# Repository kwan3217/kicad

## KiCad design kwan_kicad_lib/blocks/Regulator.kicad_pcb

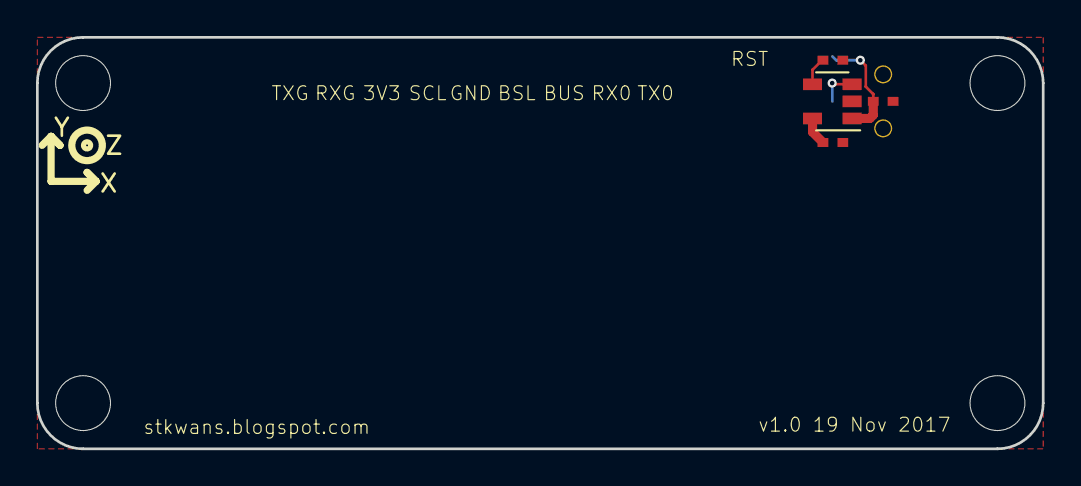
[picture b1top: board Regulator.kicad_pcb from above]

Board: 2 copper layers, 55.9 x 22.9 mm, 10 parts (0 on the bottom side), 5 nets.

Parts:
C704: 1uF; SMD_0402
C714: 100nF; SMD_0402
C715: 4.7nF; SMD_0402
JP1, JP2, JP4, JP5: STAND-OFFTIGHT; STAND-OFF-TIGHT
S701: SPDT; SWITCH_DPDT_AZY0202
U501: MPU9250; Axis
U701: 3.3V; SOT-23-5

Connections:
/BYP: C714.1, U701.4
/GND: C704.2, C714.2, C715.2, S701.3, U701.2
/PWR_EN: S701.2, U701.3
/VCC: C715.1, U701.5
/VRAW: C704.1, S701.1, U701.1

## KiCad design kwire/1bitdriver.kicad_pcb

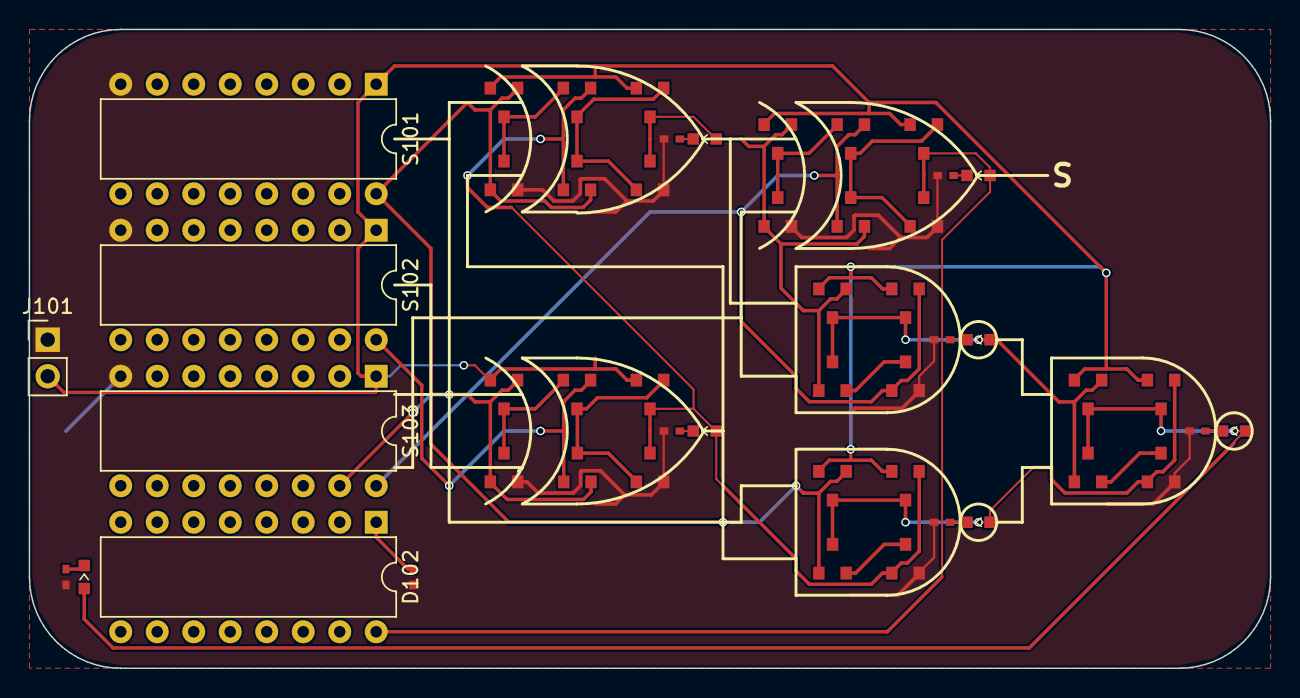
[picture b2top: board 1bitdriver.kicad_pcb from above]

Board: 2 copper layers, 86.4 x 44.5 mm, 50 parts (0 on the bottom side), 29 nets.

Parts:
D101: K; D_0603
D102: S; DIP-16_W7.62mm
D401, D501, D601, D701, D801, D901: LED_Small; D_0603
J101: CONN_01X02; Pin_Header_Straight_1x02_Pitch2.54mm
Q401, Q404, Q501, Q504, Q601, Q604, Q701, Q703, Q705, Q801, Q803, Q805, Q901, Q903, Q905: PMOS; SOT-23
Q402, Q403, Q502, Q503, Q602, Q603, Q702, Q704, Q706, Q802, Q804, Q806, Q902, Q904, Q906: NMOS; SOT-23
R101, R102, R401, R501, R601, R701, R801, R901: RESISTOR; SMD_0402
S101: A; DIP-16_W7.62mm
S102: B; DIP-16_W7.62mm
S103: C; DIP-16_W7.62mm

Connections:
/A: Q501.1, Q502.1, Q701.1, Q702.1, Q704.2, S101.16
/B: Q903.1, Q904.1, S102.16
/C: Q403.1, Q404.1, Q803.1, Q804.1, S103.16
/K: D101.2, D601.2, Q601.3, Q602.3, Q604.3
/S: D102.16, D801.2, Q805.3, Q806.3
/SUB: Q901.1, Q902.1, Q904.2, S103.15
/bit0/adder/#AandB: D501.2, Q501.3, Q502.3, Q504.3, Q603.1, Q604.1
/bit0/adder/#AxorBandC: D401.2, Q401.3, Q402.3, Q404.3, Q601.1, Q602.1
/bit0/adder/AxorB: D701.2, Q401.1, Q402.1, Q705.3, Q706.3, Q801.1, Q802.1, Q804.2
/bit0/adder/B: D901.2, Q503.1, Q504.1, Q703.1, Q704.1, Q905.3, Q906.3
GND: J101.1, Q403.2, Q503.2, Q603.2, Q702.2, Q706.2, Q802.2, Q806.2, Q902.2, Q906.2, R101.2, R102.2, R401.2, R501.2, R601.2, R701.2, R801.2, R901.2, S101.8, S102.8, S103.8
unnamed: D101.1, R101.1
unnamed: D102.1, R102.1
unnamed: D401.1, R401.1
unnamed: D501.1, R501.1
unnamed: D601.1, R601.1
unnamed: D701.1, R701.1
unnamed: D801.1, R801.1
unnamed: D901.1, R901.1
unnamed: Q402.2, Q403.3
unnamed: Q502.2, Q503.3
unnamed: Q602.2, Q603.3
unnamed: Q701.3, Q702.3, Q703.2
unnamed: Q703.3, Q704.3, Q705.1, Q706.1
unnamed: Q801.3, Q802.3, Q803.2
unnamed: Q803.3, Q804.3, Q805.1, Q806.1
unnamed: Q901.3, Q902.3, Q903.2
unnamed: Q903.3, Q904.3, Q905.1, Q906.1
VCC: J101.2, Q401.2, Q404.2, Q501.2, Q504.2, Q601.2, Q604.2, Q701.2, Q705.2, Q801.2, Q805.2, Q901.2, Q905.2, S101.1, S102.1, S103.1

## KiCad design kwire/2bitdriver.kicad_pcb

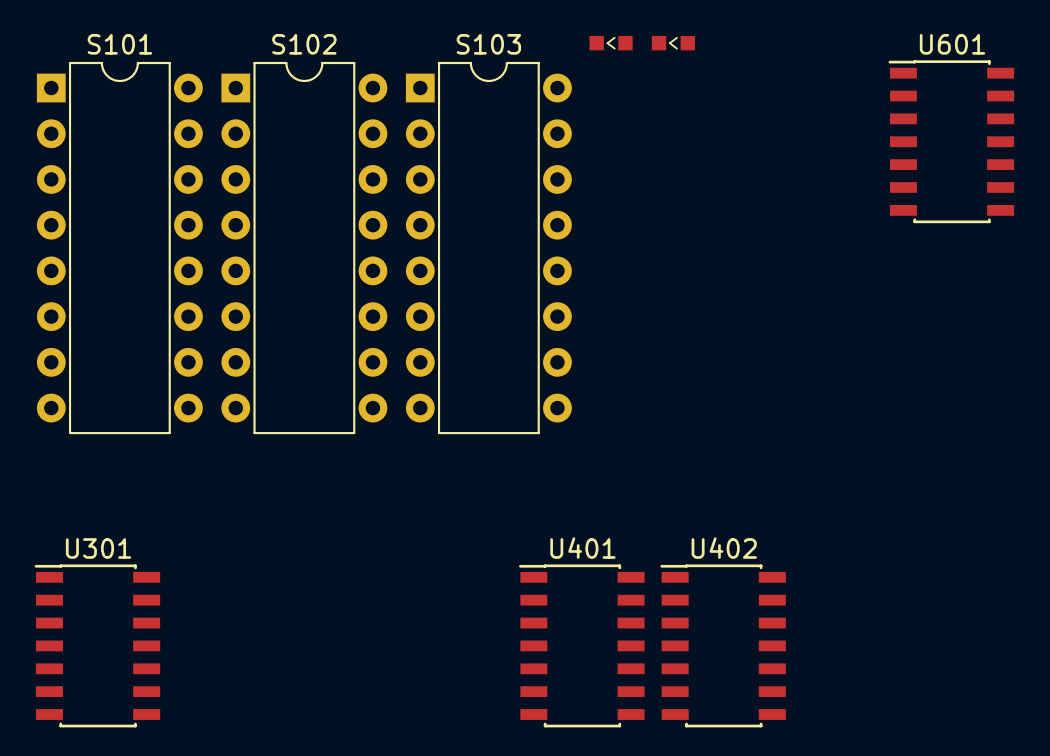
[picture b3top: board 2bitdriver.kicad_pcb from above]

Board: 2 copper layers, 9 parts (0 on the bottom side), 19 nets, no tracks yet.

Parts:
D101: K; D_0603
D102: S; D_0603
S101: A; DIP-16_W7.62mm
S102: B; DIP-16_W7.62mm
S103: C; DIP-16_W7.62mm
U301, U601: 74LS86; SOIC-14_3.9x8.7mm_Pitch1.27mm
U401: 74LS08; SOIC-14_3.9x8.7mm_Pitch1.27mm
U402: 74LS32; SOIC-14_3.9x8.7mm_Pitch1.27mm

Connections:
/A0: S101.16, U301.4, U401.4
/A1: S101.15, U401.12, U601.1
/B0: S102.16, U301.2
/B1: S102.15, U301.13
/C0: S103.16, U301.10, U401.2
/K: D101.2, U402.6
/S: D102.2, U301.8
/SUB: S103.15, U301.1, U301.12
/bit0/bit0/adder/AandB: U401.6, U402.2
/bit0/bit0/adder/AxorB: U301.6, U301.9, U401.1
/bit0/bit0/adder/AxorBandC: U401.3, U402.1
/bit0/bit0/adder/B: U301.3, U301.5, U401.5
/bit0/bit1/C_IN: U401.10, U402.3, U601.5
/bit0/bit1/adder/AandB: U401.11, U402.5
/bit0/bit1/adder/AxorB: U401.9, U601.3, U601.4
/bit0/bit1/adder/AxorBandC: U401.8, U402.4
/bit0/bit1/adder/B: U301.11, U401.13, U601.2
GND: D101.1, D102.1, S101.8, S102.8, S103.8, U301.7, U401.7, U402.7, U601.7
VCC: S101.1, S102.1, S103.1, U301.14, U401.14, U402.14, U601.14

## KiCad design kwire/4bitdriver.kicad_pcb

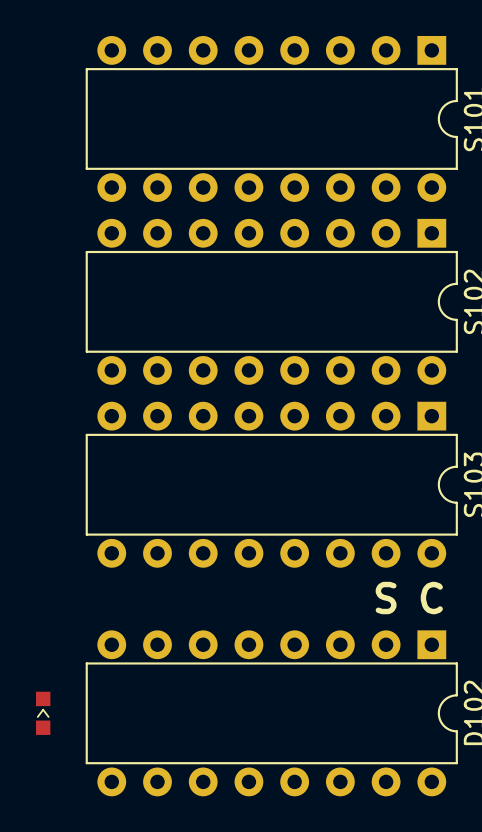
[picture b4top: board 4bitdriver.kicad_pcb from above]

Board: 2 copper layers, 5 parts (0 on the bottom side), 2 nets, no tracks yet.

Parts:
D101: K; D_0603
D102: S; DIP-16_W7.62mm
S101: A; DIP-16_W7.62mm
S102: B; DIP-16_W7.62mm
S103: C; DIP-16_W7.62mm

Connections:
GND: D101.1, D102.1, D102.2, D102.3, D102.4, D102.5, D102.6, D102.7, D102.8, S101.8, S102.8, S103.8
VCC: S101.1, S102.1, S103.1

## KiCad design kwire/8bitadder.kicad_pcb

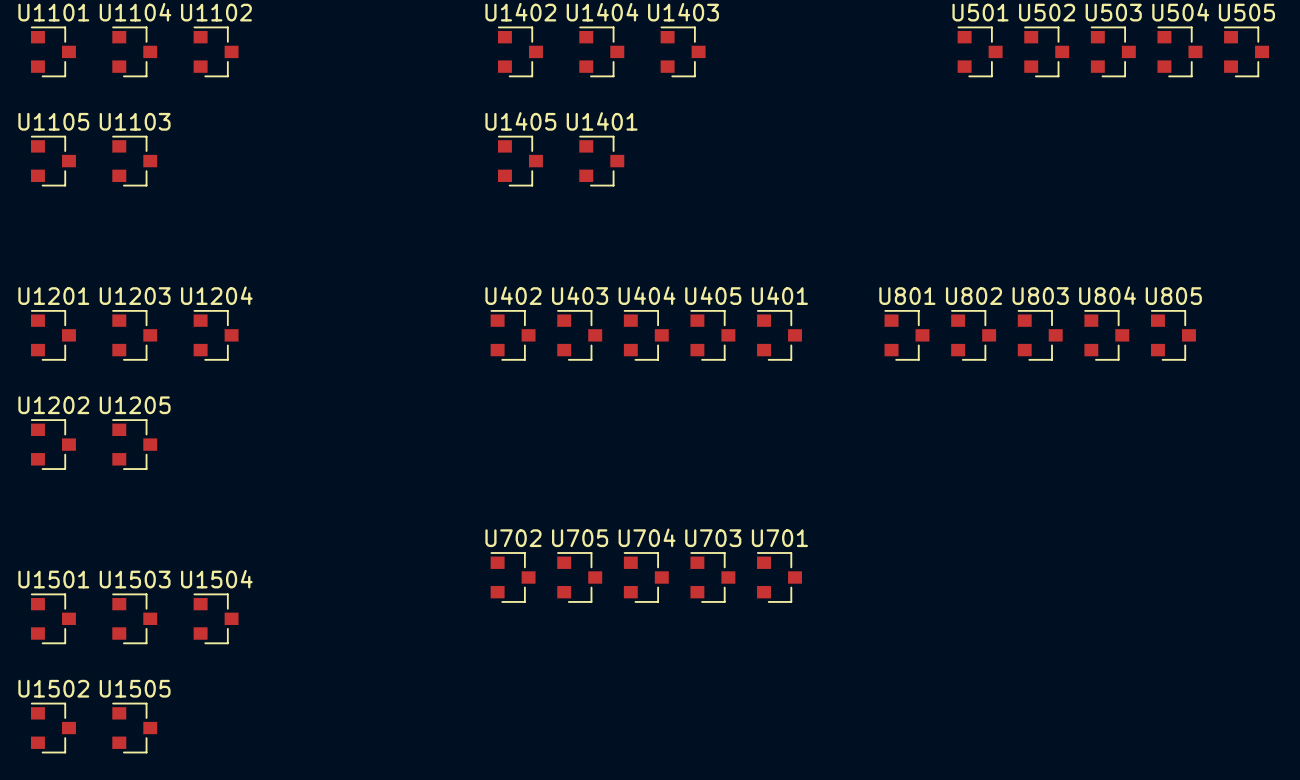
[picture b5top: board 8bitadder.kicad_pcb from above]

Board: 2 copper layers, 40 parts (0 on the bottom side), 48 nets, no tracks yet.

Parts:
U401, U404, U501, U504, U701, U704, U801, U804, U1101, U1104, U1201, U1204, U1401, U1404, U1501, U1504: XOR; SOT-23
U402, U403, U502, U503, U702, U703, U802, U803, U1102, U1103, U1202, U1203, U1402, U1403, U1502, U1503: AND; SOT-23
U405, U505, U705, U805, U1105, U1205, U1405, U1505: OR; SOT-23

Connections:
/A0: U401.1, U403.1
/A1: U501.1, U503.1
/A2: U701.1, U703.1
/A3: U801.1, U803.1
/A4: U1101.1, U1103.1
/A5: U1201.1, U1203.1
/A6: U1401.1, U1403.1
/A7: U1501.1, U1503.1
/B0: U401.2, U403.2
/B1: U501.2, U503.2
/B2: U701.2, U703.2
/B3: U801.2, U803.2
/B4: U1101.2, U1103.2
/B5: U1201.2, U1203.2
/B6: U1401.2, U1403.2
/B7: U1501.2, U1503.2
/C0: U402.2, U404.2
/bit03/bit01/bit1/C_IN: U405.3, U502.2, U504.2
/bit03/bit23/C0: U505.3, U702.2, U704.2
/bit03/bit23/bit1/C_IN: U705.3, U802.2, U804.2
/bit47/C0: U805.3, U1102.2, U1104.2
/bit47/bit01/bit1/C_IN: U1105.3, U1202.2, U1204.2
/bit47/bit23/C0: U1205.3, U1402.2, U1404.2
/bit47/bit23/bit1/C_IN: U1405.3, U1502.2, U1504.2
unnamed: U401.3, U402.1, U404.1
unnamed: U402.3, U405.1
unnamed: U403.3, U405.2
unnamed: U501.3, U502.1, U504.1
unnamed: U502.3, U505.1
unnamed: U503.3, U505.2
unnamed: U701.3, U702.1, U704.1
unnamed: U702.3, U705.1
unnamed: U703.3, U705.2
unnamed: U801.3, U802.1, U804.1
unnamed: U802.3, U805.1
unnamed: U803.3, U805.2
unnamed: U1101.3, U1102.1, U1104.1
unnamed: U1102.3, U1105.1
unnamed: U1103.3, U1105.2
unnamed: U1201.3, U1202.1, U1204.1
unnamed: U1202.3, U1205.1
unnamed: U1203.3, U1205.2
unnamed: U1401.3, U1402.1, U1404.1
unnamed: U1402.3, U1405.1
unnamed: U1403.3, U1405.2
unnamed: U1501.3, U1502.1, U1504.1
unnamed: U1502.3, U1505.1
unnamed: U1503.3, U1505.2
